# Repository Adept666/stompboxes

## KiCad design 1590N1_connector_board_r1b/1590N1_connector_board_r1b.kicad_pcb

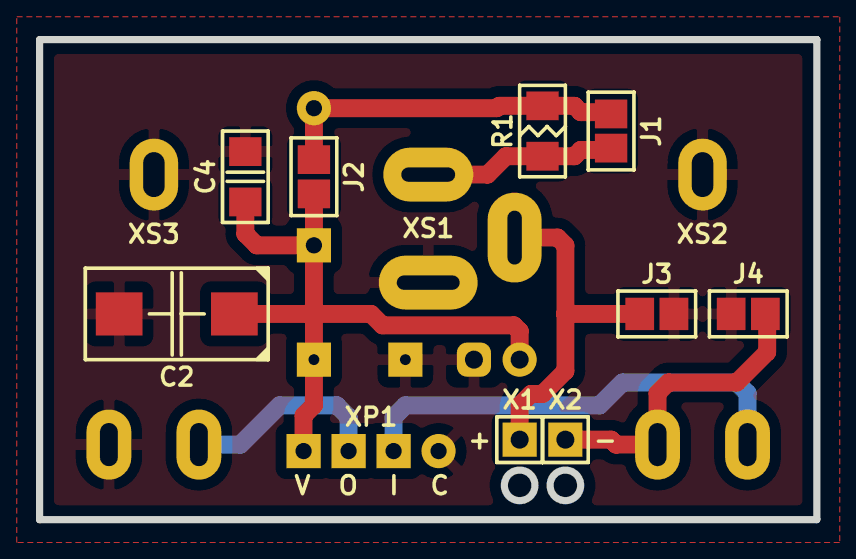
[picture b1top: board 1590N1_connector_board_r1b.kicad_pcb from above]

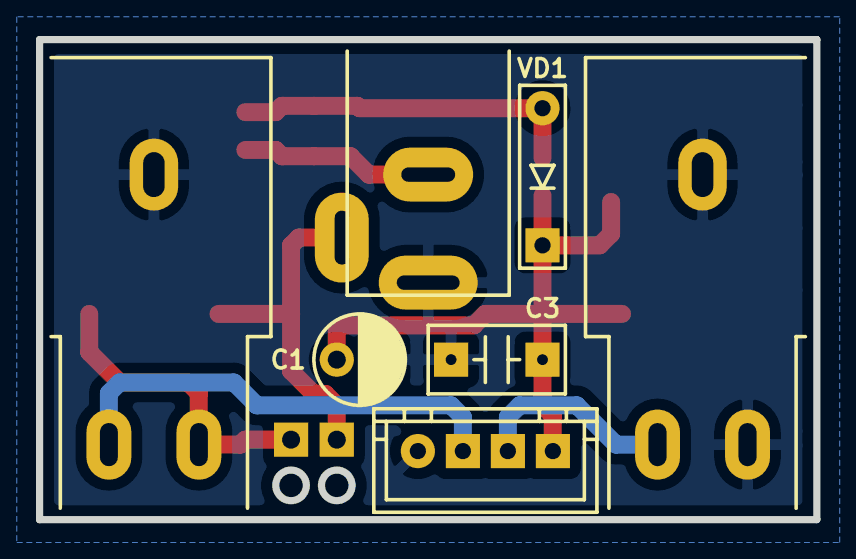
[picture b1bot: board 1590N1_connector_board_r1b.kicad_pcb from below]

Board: 2 copper layers, 43.2 x 26.7 mm, 17 parts (7 on the bottom side), 8 nets.

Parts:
C1: 107; CP-RADIAL-D05.0-P02.0-CLS
C2: 107; CP-CTSMD-D
C3: 104; C-DISK-D04.2-T03.0-P05.08-d0.5
C4: 104; C-SM-1206
GB1: PP3; B-PP3-HV
J1: J1; J-SB-1206-2
J2: J2; J-SB-1206-2
J3: J3; J-SB-1206-2
J4: J4; J-SB-1206-2
R1: 330; R-SM-1206
VD1: 5817; P-DO-41
X1: +; CON-PAD-S-1.0-1.9
X2: -; CON-PAD-S-1.0-1.9
XP1: B4B-XH-A; CON-XH-B4B-A
XS1: DC-005; CON-DC-005-9V-OVAL
XS2: PJ-651A-01; CON-PJ-651A-01-IN-OVAL
XS3: PJ-651A-01; CON-PJ-651A-01-OUT-OVAL

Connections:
/IN-CON: XP1.2, XS2.T
/OUT-CON: XP1.3, XS3.T
/PP3-NEG: J4.1, X2.1, XS2.R
/PP3-POS: J3.1, X1.1, XS1.SN
COM: C1.-, C2.-, C3.2, C4.2, J3.2, J4.2, XP1.1, XS1.C, XS2.S, XS3.R, XS3.S
unnamed: J1.1, R1.1, XS1.S
unnamed: J1.2, J2.1, R1.2, VD1.A
V: C1.+, C2.+, C3.1, C4.1, J2.2, VD1.C, XP1.4

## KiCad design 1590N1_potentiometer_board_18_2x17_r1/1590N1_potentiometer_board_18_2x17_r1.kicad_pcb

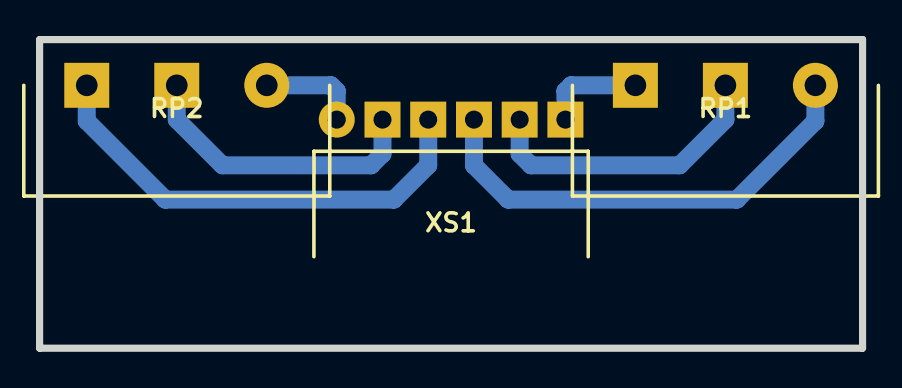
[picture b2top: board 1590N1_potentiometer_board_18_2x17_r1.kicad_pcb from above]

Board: 2 copper layers, 45.7 x 17.1 mm, 3 parts (0 on the bottom side), 6 nets.

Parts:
RP1: RP1: 16/17; RP-PDB181-K-20-P
RP2: RP2: 16/17; RP-PDB181-K-20-P
XS1: PBS-06R; CON-PBS-06R

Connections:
unnamed: RP1.1, XS1.4
unnamed: RP1.2, XS1.5
unnamed: RP1.3, XS1.6
unnamed: RP2.1, XS1.1
unnamed: RP2.2, XS1.2
unnamed: RP2.3, XS1.3

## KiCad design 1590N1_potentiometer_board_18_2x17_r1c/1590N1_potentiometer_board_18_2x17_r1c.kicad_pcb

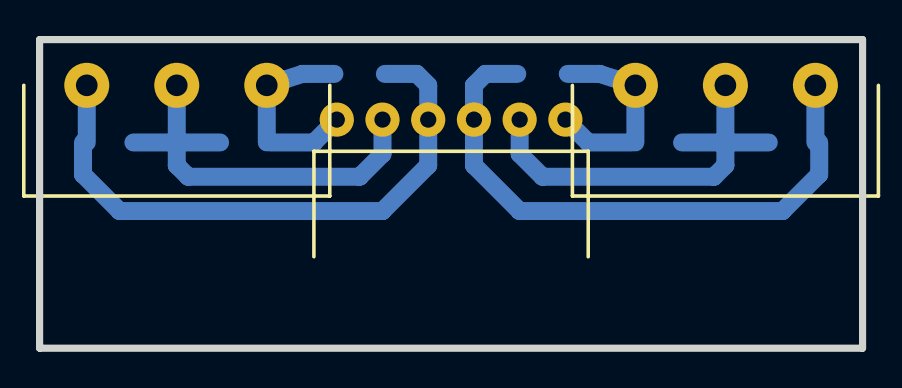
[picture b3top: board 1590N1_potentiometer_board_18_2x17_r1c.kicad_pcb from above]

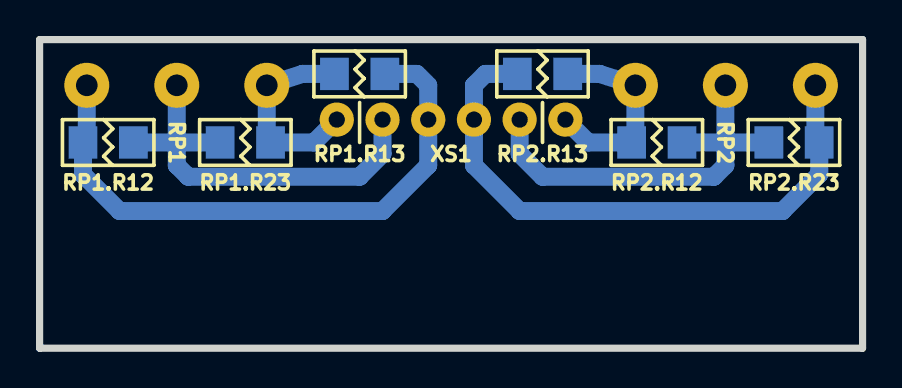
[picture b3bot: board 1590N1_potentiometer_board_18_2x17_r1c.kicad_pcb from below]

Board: 2 copper layers, 45.7 x 17.1 mm, 9 parts (6 on the bottom side), 6 nets.

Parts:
RP1: RP1: 16/17; RP-PDB181-K-20-P-CIRCULAR
RP1.R12, RP1.R13, RP1.R23, RP2.R12, RP2.R13, RP2.R23: X; R-SM-1206
RP2: RP2: 16/17; RP-PDB181-K-20-P-CIRCULAR
XS1: PBS-06R; CON-PBS-06R-CIRCULAR

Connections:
unnamed: RP1.1, RP1.R12.2, RP1.R13.2, XS1.4
unnamed: RP1.2, RP1.R12.1, RP1.R23.2, XS1.5
unnamed: RP1.3, RP1.R13.1, RP1.R23.1, XS1.6
unnamed: RP2.1, RP2.R12.2, RP2.R13.2, XS1.1
unnamed: RP2.2, RP2.R12.1, RP2.R23.2, XS1.2
unnamed: RP2.3, RP2.R13.1, RP2.R23.1, XS1.3

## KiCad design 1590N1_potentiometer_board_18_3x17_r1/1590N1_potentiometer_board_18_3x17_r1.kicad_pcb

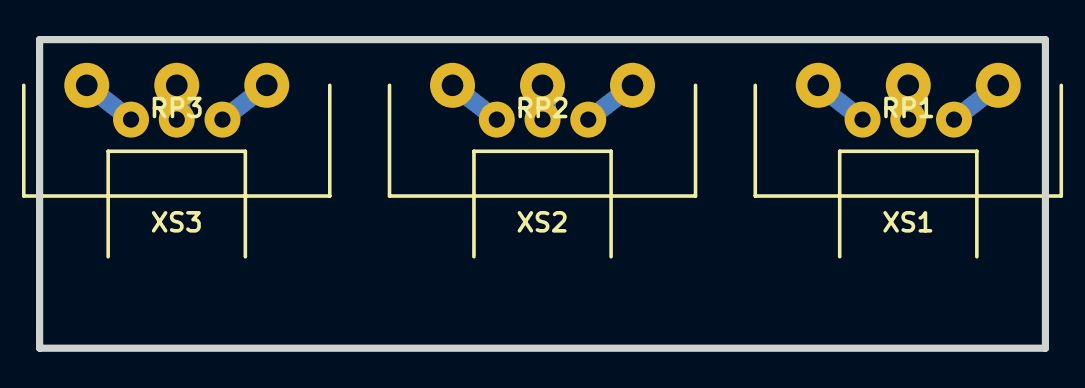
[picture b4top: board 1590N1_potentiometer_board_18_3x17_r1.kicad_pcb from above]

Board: 2 copper layers, 55.9 x 17.1 mm, 6 parts (0 on the bottom side), 9 nets.

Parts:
RP1: RP1: 16/17; RP-PDB181-K-20-P-CIRCULAR
RP2: RP2: 16/17; RP-PDB181-K-20-P-CIRCULAR
RP3: RP3: 16/17; RP-PDB181-K-20-P-CIRCULAR
XS1, XS2, XS3: PBS-03R; CON-PBS-03R-CIRCULAR

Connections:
unnamed: RP1.1, XS1.3
unnamed: RP1.2, XS1.2
unnamed: RP1.3, XS1.1
unnamed: RP2.1, XS2.3
unnamed: RP2.2, XS2.2
unnamed: RP2.3, XS2.1
unnamed: RP3.1, XS3.3
unnamed: RP3.2, XS3.2
unnamed: RP3.3, XS3.1

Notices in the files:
1590N1_connector_board_r1b/1590N1_connector_board_r1b.kicad_pcb:
This project is licensed under GNU General Public License v3.0 or later
